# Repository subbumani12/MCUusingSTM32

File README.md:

# MCUusingSTM32
A microcontroller development board designed in KiCad. Uses an STM32 F1 Series MC with Micro USB interfacing, inbuilt 16MHz Crystal Oscillator and USART and I2C Communication Protocol.

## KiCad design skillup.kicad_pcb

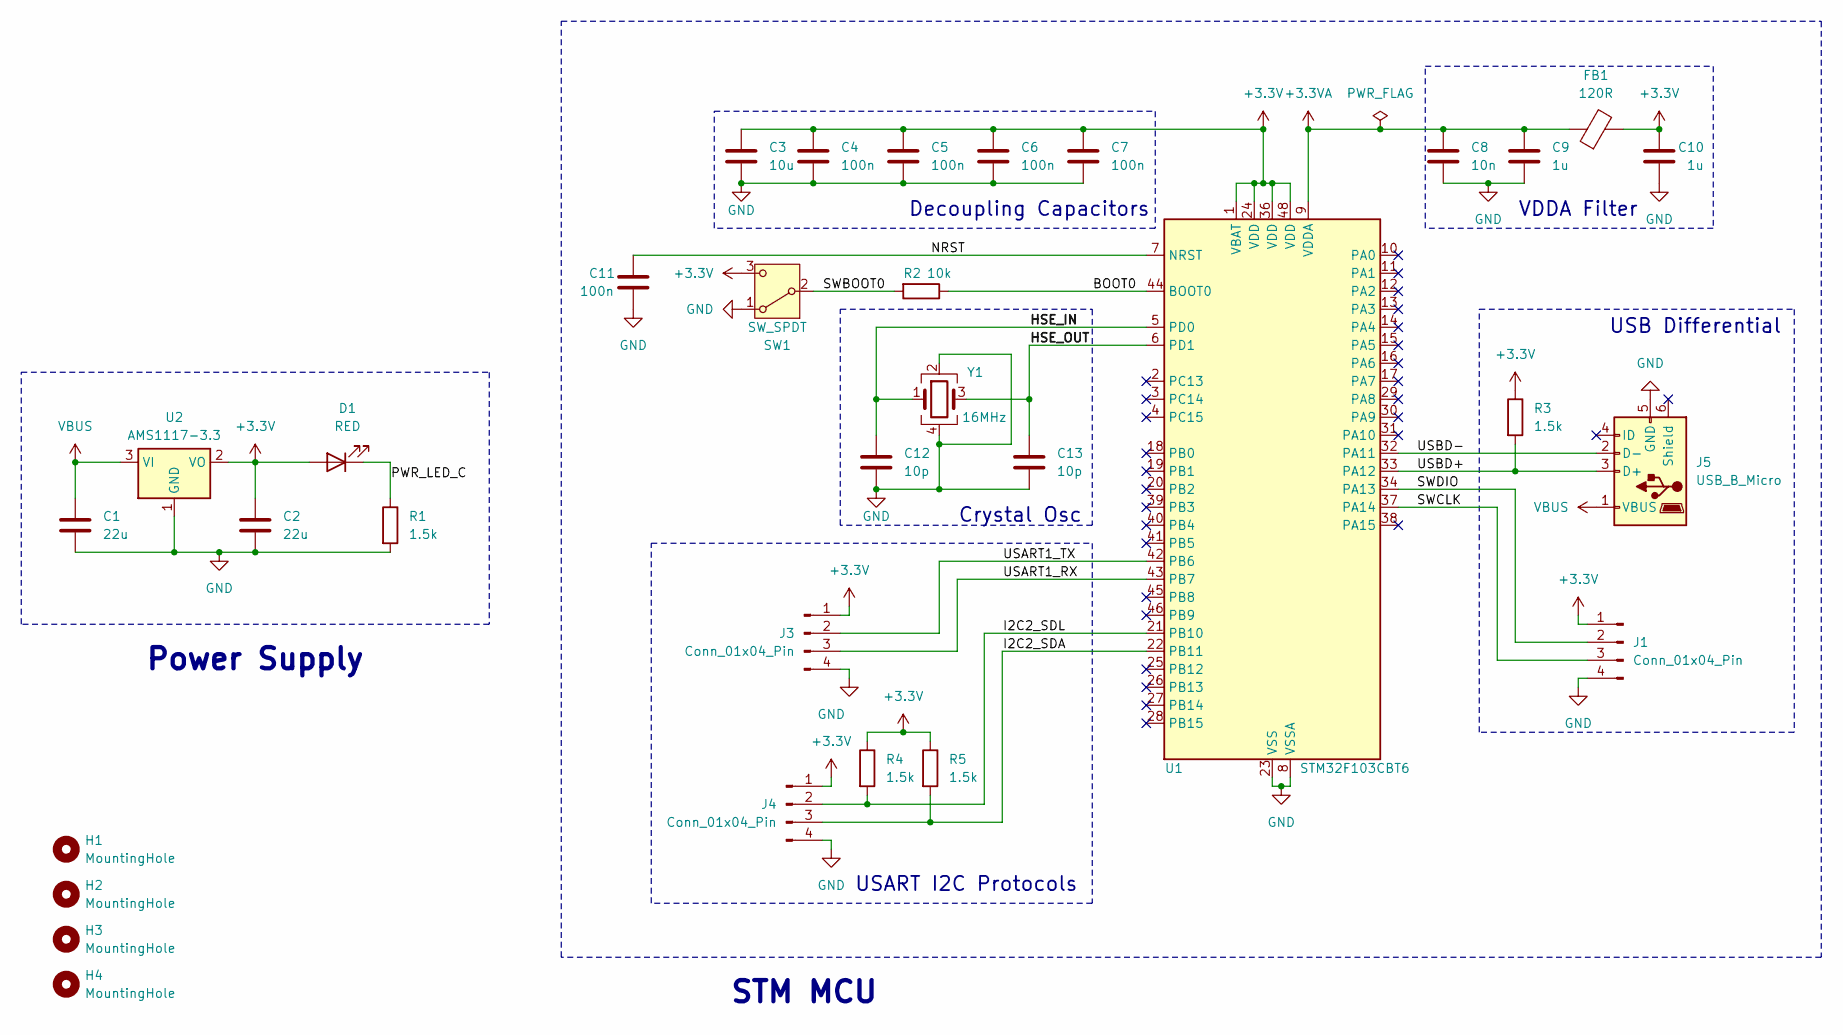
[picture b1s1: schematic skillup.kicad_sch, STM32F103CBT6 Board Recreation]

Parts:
C1, C2: 22u; C_0805_2012Metric
C3: 10u; C_0603_1608Metric
C4, C5, C6, C7, C11: 100n; C_0402_1005Metric
C8: 10n; C_0402_1005Metric
C9, C10: 1u; C_0402_1005Metric
C12, C13: 10p; C_0402_1005Metric
D1: RED; LED_0603_1608Metric
FB1: 120R; L_0603_1608Metric
H1, H2, H3, H4: MountingHole; MountingHole_2.2mm_M2
J1, J3, J4: Conn_01x04_Pin; PinHeader_1x04_P2.54mm_Vertical
J5: USB_B_Micro; USB_Micro-B_Wuerth_629105150521
R1, R3, R4, R5: 1.5k; R_0402_1005Metric
R2: 10k; R_0402_1005Metric
SW1: SW_SPDT; SW_SPDT_PCM12
U1: STM32F103CBT6; LQFP-48_7x7mm_P0.5mm
U2: AMS1117-3.3; SOT-223-3_TabPin2
Y1: 16MHz; Crystal_SMD_3225-4Pin_3.2x2.5mm

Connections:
+3.3V: C2.1, C3.1, C4.1, C5.1, C6.1, C7.1, C10.1, D1.2 (A), FB1.2, J1.1, J3.1, J4.1, R3.1, R4.1, R5.1, SW1.3 (C), U1.1 (VBAT), U1.24 (VDD), U1.36 (VDD), U1.48 (VDD), U2.2 (VO)
+3.3VA: C8.1, C9.1, FB1.1, U1.9 (VDDA)
/BOOT0: R2.1, U1.44 (BOOT0)
/HSE_IN: C12.1, U1.5 (PD0), Y1.1
/HSE_OUT: C13.1, U1.6 (PD1), Y1.3
/I2C2_SDA: J4.3, R5.2, U1.22 (PB11)
/I2C2_SDL: J4.2, R4.2, U1.21 (PB10)
/NRST: C11.1, U1.7 (NRST)
/PWR_LED_C: D1.1 (K), R1.1
/SWBOOT0: R2.2, SW1.2 (B)
/SWCLK: J1.3, U1.37 (PA14)
/SWDIO: J1.2, U1.34 (PA13)
/USART1_RX: J3.3, U1.43 (PB7)
/USART1_TX: J3.2, U1.42 (PB6)
/USBD+: J5.3 (D+), R3.2, U1.33 (PA12)
/USBD-: J5.2 (D-), U1.32 (PA11)
GND: C1.2, C2.2, C3.2, C4.2, C5.2, C6.2, C7.2, C8.2, C9.2, C10.2, C11.2, C12.2, C13.2, J1.4, J3.4, J4.4, J5.5 (GND), R1.2, SW1.1 (A), U1.8 (VSSA), U1.23 (VSS), U1.35 (VSS), U1.47 (VSS), U2.1 (GND), Y1.2, Y1.4
VBUS: C1.1, J5.1 (VBUS), U2.3 (VI)

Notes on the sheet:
Decoupling Capacitors
VDDA Filter
STM MCU
USB Differential
Crystal Osc
USART I2C Protocols
Power Supply

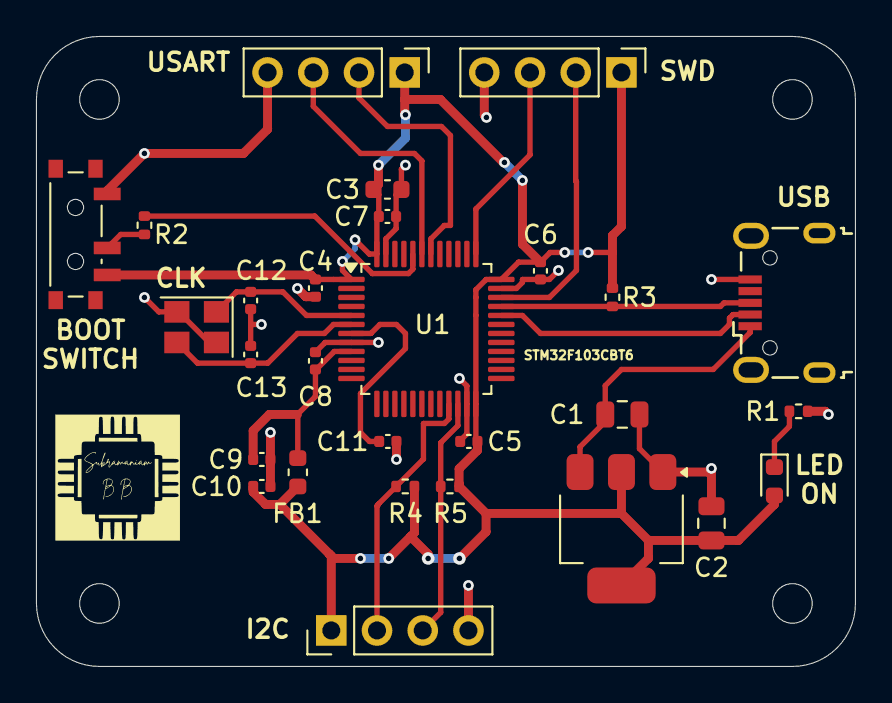
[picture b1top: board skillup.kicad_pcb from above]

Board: 2 copper layers, 45.5 x 35.0 mm, 32 parts (0 on the bottom side), 18 nets.
